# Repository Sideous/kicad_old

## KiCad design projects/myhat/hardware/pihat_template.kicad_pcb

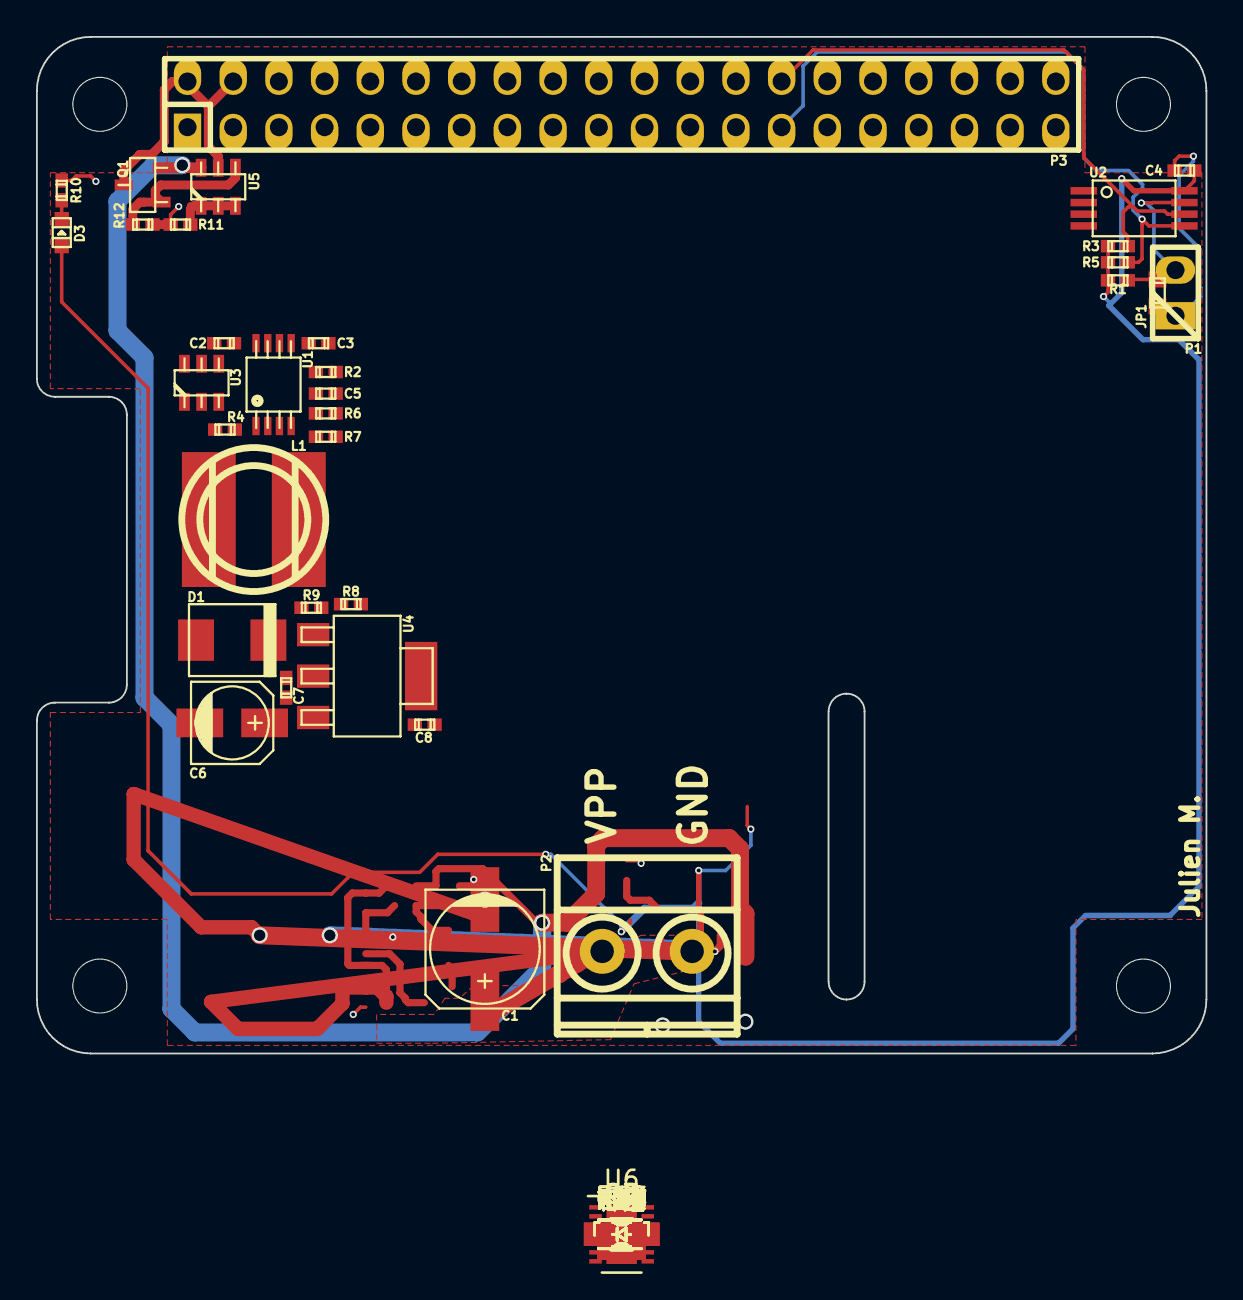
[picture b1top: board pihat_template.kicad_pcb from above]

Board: 2 copper layers, 65.0 x 56.5 mm, 56 parts (0 on the bottom side), 34 nets.

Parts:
C1: 50uf/50v; c_elec_6.3x7.7
C2, C4, C5, C7: 0.1uf; c_0402
C3: 1nf; c_0402
C6: 10uf/6.3V; c_elec_4x5.3
C8: 1uf; c_0402
C9: 1uF; C_0603_HandSoldering
C10, C11: 0.47uF; C_0603_HandSoldering
D1: DIODESCH; do214aa
D2: 18V; SOD-323
D3: LED; Led_0603
D4, D5, D6: 5.6V; SOD-323
JP1: JUMPER; r_0603
L1: 22uH; inductor_smd_8x5mm
P1: CONN_01X02; pin_strip_2
P2: CONN_01X02; mkds_1,5-2
P3: Raspberry_Pi_+_Conn; pin_socket_20x2
Q1: BSS138; sot23
Q2, Q3: BSS138; SOT-23
R1: 1k; r_0402
R2: 24k; r_0402
R3, R5: 3.9k; r_0402
R4: 270; r_0402
R6: 30k; r_0402
R7, R11: 10k; r_0402
R8: 390; r_0402
R9: 240; r_0402
R10: 360; r_0402
R12: 47k; r_0402
R13: 2.0M; R_0805_HandSoldering
R14: 300K; R_0603_HandSoldering
R15: 200k; R_0603_HandSoldering
R16, R17: 10K; R_0603_HandSoldering
R18: 510K; R_0603_HandSoldering
R19: 1M; R_0603_HandSoldering
R20: 0.01; R_0805_HandSoldering
R21: 1K; R_0603_HandSoldering
R22, R23: 150; R_0603_HandSoldering
TH1, TH2: 10K NTC; R_0402
U1: LM3489; msoic-8
U2: CAT24C32HU4I-GT3; tssop-8
U3: FDC5614P; sot23-6
U4: LM1117IMPX-ADJ; sot223
U5: DMMT5401; sot23-6
U6: MAX17205; DFN-14-1EP_3x4mm_Pitch0.5mm

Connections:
+3V3: C4.1, C7.1, C8.1, D3.1, R1.1, R3.1, R5.1, R9.1, U2.8, U4.2
+5V: C5.1, C6.1, L1.2, Q1.3, R6.1, U4.3, U5.6
+24V: C1.1, C2.1, C3.1, P2.1, R2.1, U1.8, U3.4
/Back Power Protection/5V_MCU: P3.2, P3.4, Q1.2, U5.5
/hat options/Bat_-: R20.1, U6.4
/hat options/Ext_+: Q3.3, R13.1, R18.1
GND: C1.2, C2.2, C4.2, C6.2, C7.2, C8.2, D1.1, JP1.2, P1.1, P2.2, P3.6, P3.9, P3.14, P3.20, P3.25, P3.30, P3.34, P3.39, R7.2, R8.2, R10.2, R11.2, R12.2, U1.2, U1.6, U2.1, U2.2, U2.3, U2.4
GNDA: C9.2, C10.2, C11.2, D2.2, D4.2, D5.2, D6.2, R15.2, R19.1, R20.2, TH1.1, TH2.1, U6.2, U6.7
unnamed: C3.2, R2.2, U1.5
unnamed: C5.2, R6.2, R7.1, U1.4
unnamed: C9.1, Q3.2, U6.5
unnamed: C10.1, U6.3
unnamed: C11.1, U6.1
unnamed: D1.2, L1.1, R4.1, U3.1, U3.2, U3.5, U3.6
unnamed: D2.1, Q3.1, R18.2
unnamed: D3.2, R10.1
unnamed: D4.1, R21.2, U6.8
unnamed: D5.1, R22.2, U6.12
unnamed: D6.1, R23.2, U6.11
unnamed: JP1.1, P1.2, R1.2, U2.7
unnamed: P3.27, R5.2, U2.5
unnamed: P3.28, R3.2, U2.6
unnamed: Q1.1, R12.1, U5.4
unnamed: Q2.1, R19.2, U6.6
unnamed: Q2.2, R15.1, U6.13
unnamed: Q2.3, R14.2
unnamed: R4.2, U1.1
unnamed: R8.1, R9.2, U4.1
unnamed: R11.1, U5.1, U5.2, U5.3
unnamed: R13.2, R14.1
unnamed: R16.1, TH1.2, U6.9
unnamed: R16.2, R17.2, U6.14
unnamed: R17.1, TH2.2, U6.10
unnamed: U1.7, U3.3

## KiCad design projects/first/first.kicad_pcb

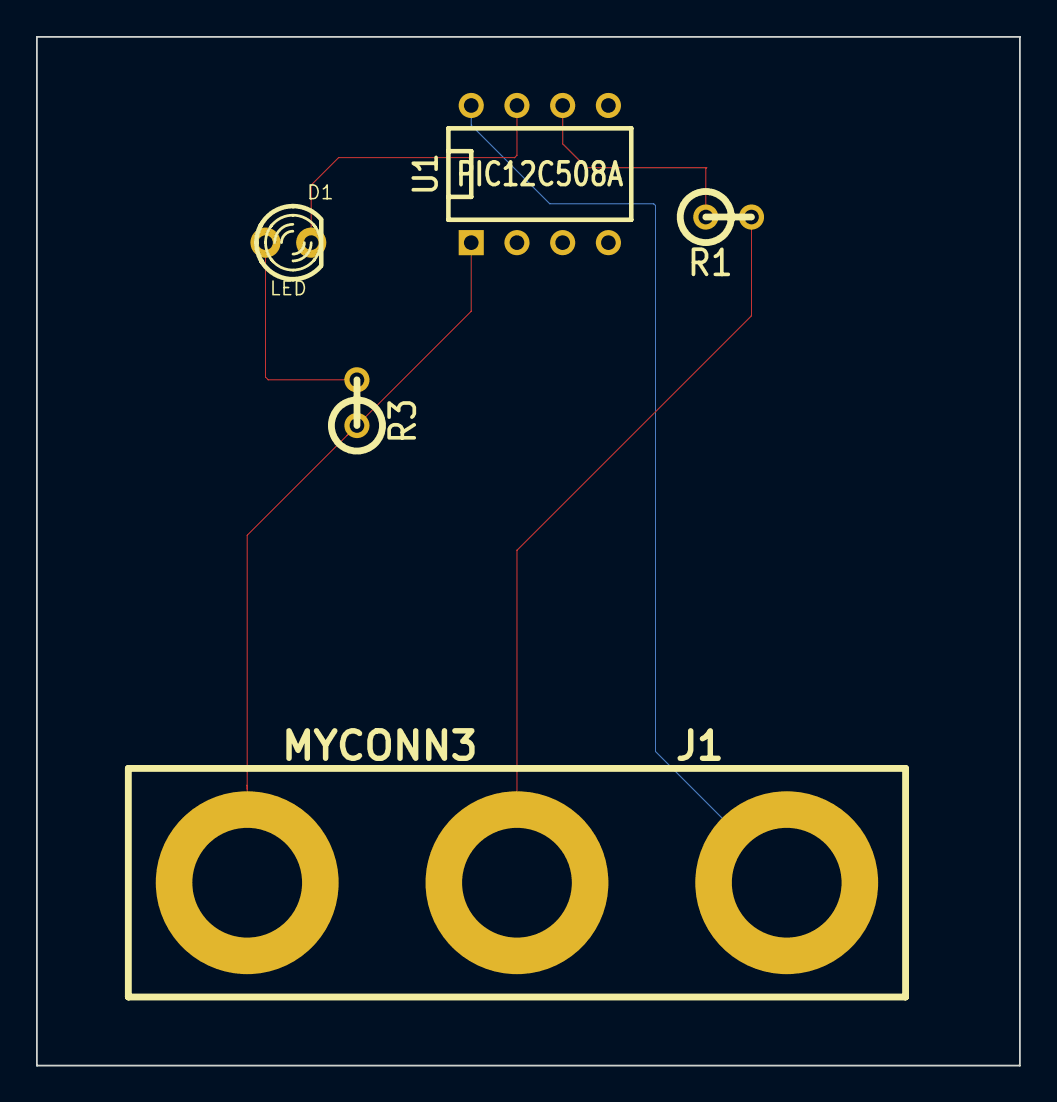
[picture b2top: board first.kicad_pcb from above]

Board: 2 copper layers, 54.6 x 57.1 mm, 5 parts (0 on the bottom side), 6 nets.

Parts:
D1: LED; LED-3MM
J1: MYCONN3; 3PIN_6mm
R1: 100; R1
R3: R; R1
U1: PIC12C508A; DIP-8__300

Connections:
/input: R1.1, U1.6
/uctoled: D1.2, U1.7
GND: J1.3, U1.8
unnamed: J1.2, R1.2
unnamed: D1.1, R3.2
VCC: J1.1, R3.1, U1.1

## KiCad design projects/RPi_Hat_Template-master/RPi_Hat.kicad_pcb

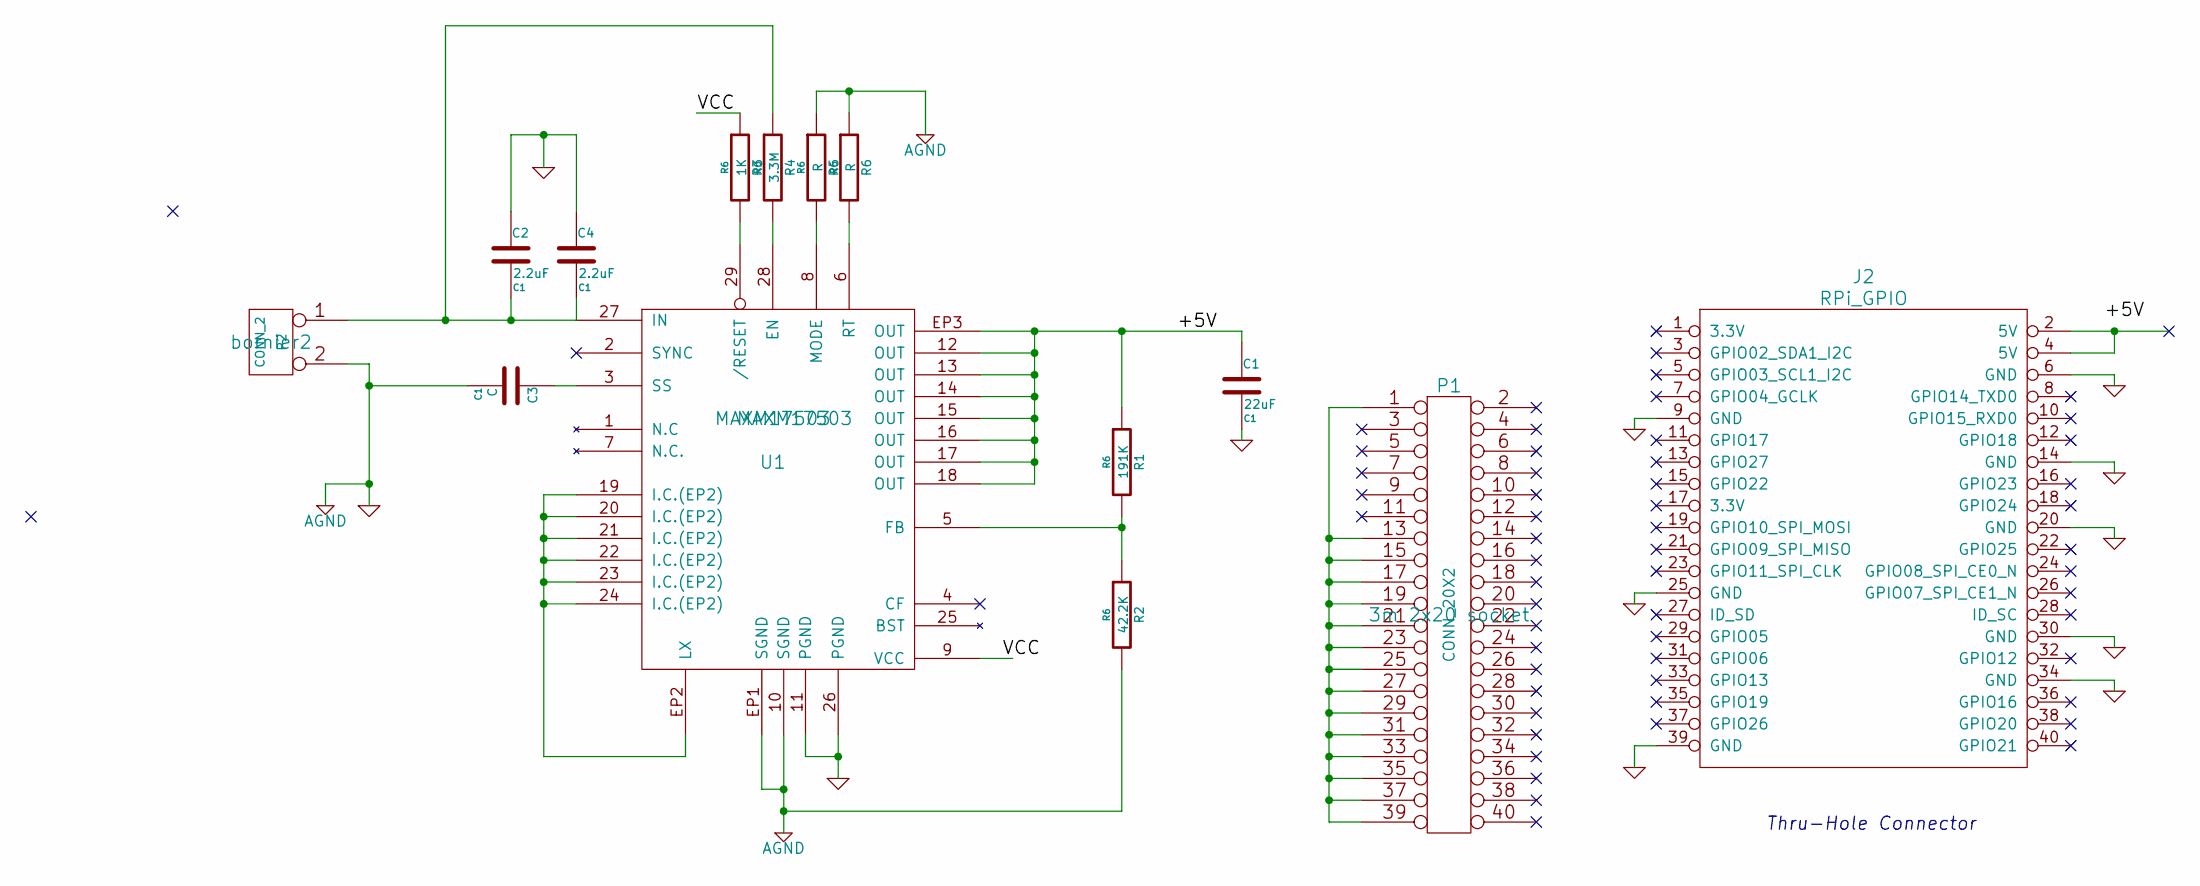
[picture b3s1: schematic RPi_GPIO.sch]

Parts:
C1: 22uF; C1
C2, C4: 2.2uF; C1
C3: C; C1
J2: RPi_GPIO; 3m 2x20 socket
P1: CONN_20X2; 3m 2x20 socket
P2: CONN_2; bornier2
R1: 191K; R6
R2: 42.2K; R6
R3: 1K; R6
R4: 3.3M; R6
R5, R6: R; R6
U1: MAXM17503

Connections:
/RPi_GPIO/+5V: C1.1, R1.1, U1.12 (OUT), U1.13 (OUT), U1.14 (OUT), U1.15 (OUT), U1.16 (OUT), U1.17 (OUT), U1.18 (OUT), U1.EP3 (OUT)
/RPi_GPIO/VCC: R3.1, U1.9 (VCC)
AGND: C1.2, C2.1, C3.2, C4.1, J2.6 (GND), J2.9 (GND), J2.14 (GND), J2.20 (GND), J2.25 (GND), J2.30 (GND), J2.34 (GND), J2.39 (GND), P2.2 (PM), R2.2, R5.1, R6.1, U1.10 (SGND), U1.11 (PGND), U1.26 (PGND), U1.EP1 (SGND)
unnamed: R6.2, U1.6 (RT)
unnamed: R5.2, U1.8 (MODE)
unnamed: R4.2, U1.28 (EN)
unnamed: R3.2, U1.29 (/RESET)
unnamed: C3.1, U1.3 (SS)
unnamed: J2.2 (5V), J2.4 (5V)
unnamed: P1.1, P1.13, P1.15, P1.17, P1.19, P1.21, P1.23, P1.25, P1.27, P1.29, P1.31, P1.33, P1.35, P1.37, P1.39
unnamed: C2.2, C4.2, P2.1, R4.1, U1.27 (IN)
unnamed: U1.19 (I.C.(EP2)), U1.20 (I.C.(EP2)), U1.21 (I.C.(EP2)), U1.22 (I.C.(EP2)), U1.23 (I.C.(EP2)), U1.24 (I.C.(EP2)), U1.EP2 (LX)
unnamed: R1.2, R2.1, U1.5 (FB)

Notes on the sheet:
Thru-Hole Connector

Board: 2 copper layers, 14 parts (0 on the bottom side), 13 nets, no tracks yet.

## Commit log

2016-11-19 Initial kicad directory
2016-11-21 Started placement of MAXM17503
2016-11-21 update part placement 11-21-16
2016-11-23 created myhat
2016-11-24 added max17205 to jvm.lib
2016-11-26 added max17205 to myhat
2016-11-28 entered components on myhat for max17205
2016-12-01 updated footprints
2016-12-02 set component values for fuel gauge
2016-12-03 updated hat_options
2016-12-15 Added footprint for MAX17205

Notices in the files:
projects/myhat/hardware/pihat_template.kicad_pcb:
License: CERN OHL V1.2
CERN OHL V1.2
